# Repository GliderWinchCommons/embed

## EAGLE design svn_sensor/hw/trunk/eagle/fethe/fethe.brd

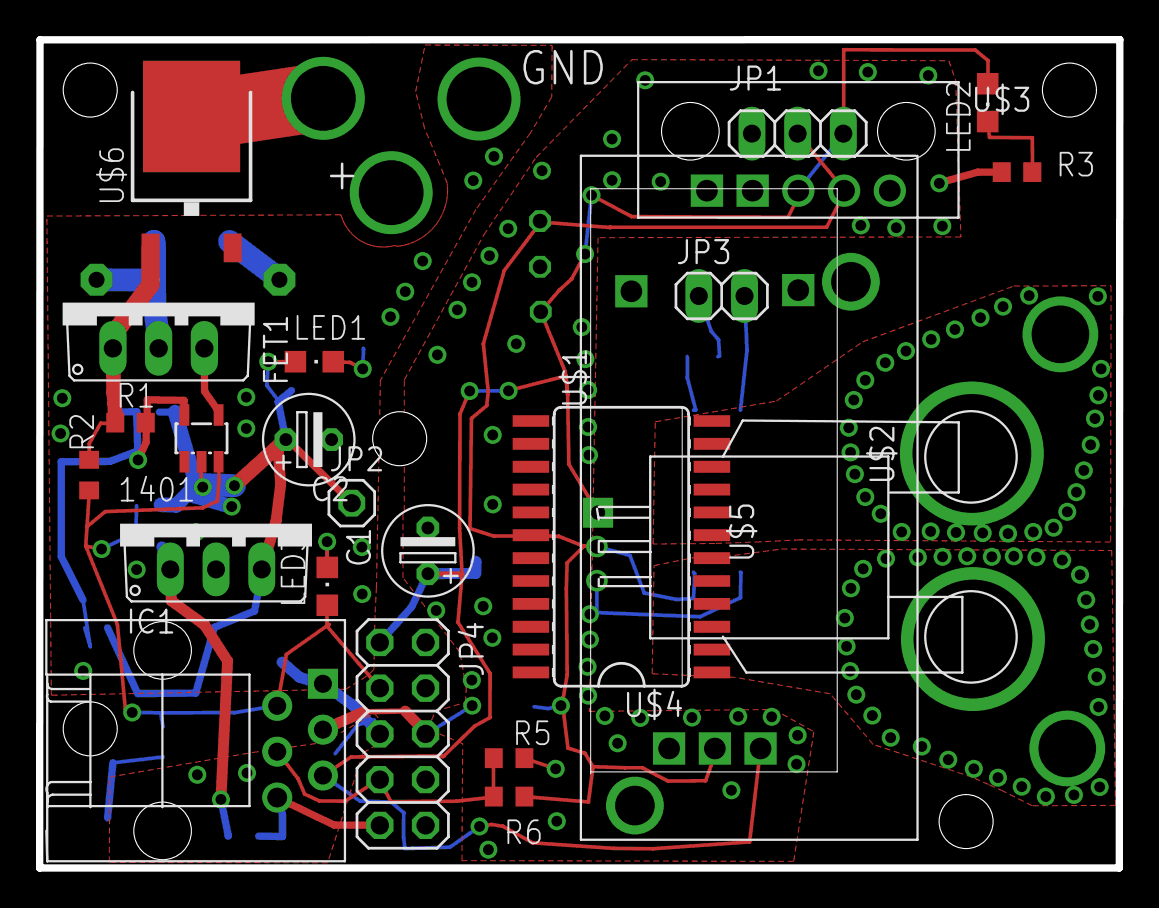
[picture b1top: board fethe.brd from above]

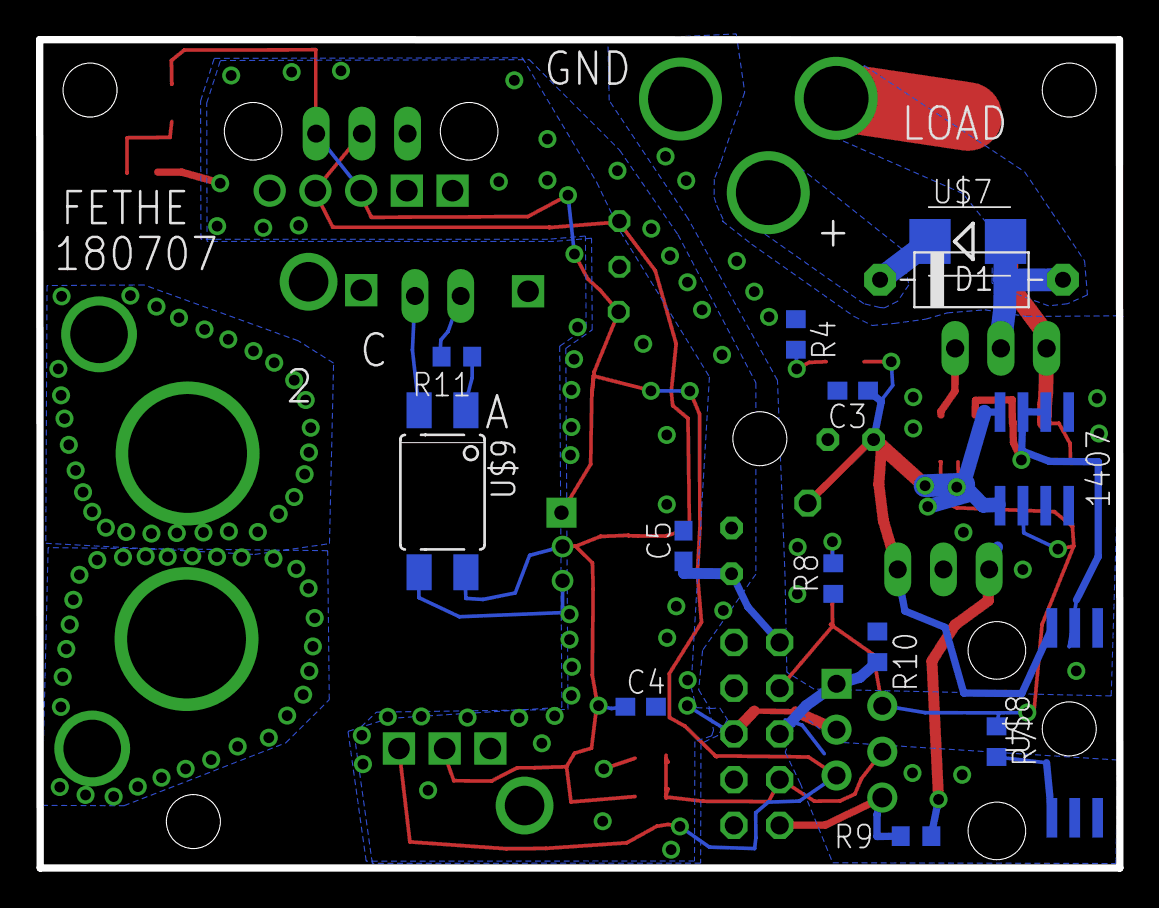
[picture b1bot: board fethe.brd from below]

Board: 2 copper layers, 60.0 x 46.0 mm, 38 parts (14 on the bottom side), 22 nets.

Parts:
1401: MCP1401; SOT23-5
1407: MCP1407; SO8
C1, C2: 10@25V; ES-2,5L
C3, C4, C5: 4.7u; C0603
D1: D-10
FET1: any1; TO220V
IC1: LM78xx; TO220V
JP1: 1X03
JP2: 1X01
JP3: 1X02
JP4: 2X05
LED1, LED2, LED3: CHIPLED_0805
R1: 4.7; R0603
R2, R9, R10: zero; R0603
R3, R6, R7, R8: 1K; R0603
R4, R11: 2.2K; R0603
R5: 3.3K; R0603
U$1: TAMURA_HE
U$2: ACS712MODULE
U$3: ACS711MODULE
U$4: ACS709/710; SO24W
U$5: ACS755
U$6: NFET-DT; D-PAK-4
U$7: B100LB; SMB_1
U$8: SI826; SDIP6
U$9: LTV817S; LTV316
U$25: MOD6P6C_1

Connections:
+5V: C1.1, C5.1, JP1.1, JP4.1, LED2.A, U$1.3, U$2.V, U$3.VCC, U$5.VCC, U$25.5
+10V: 1401.2, 1407.1, 1407.8, C2.1, C3.1, IC1.3, JP2.1, LED1.A, U$8.6
B5BUF: 1401.3, 1407.2, JP4.3, LED3.A, R2.2, R7.1, U$25.2
DIV1: JP4.7, R5.2, R6.1, U$25.4
DRV_OUT: 1401.5, 1407.6, 1407.7, R1.2, U$8.5
FET-DRAIN: D1.1, FET1.2, U$6.D, U$7.A
FET_DRIVE_1: FET1.1, R1.1, R2.1, U$6.G
GND: 1401.4, 1407.4, 1407.5, C1.2, C2.2, C3.2, C4.2, C5.2, FET1.3, IC1.2, JP1.3, JP4.6, R3.1, R4.1, R5.1, R8.1, R10.1, U$1.2, U$2.G, U$3.GND, U$3.GND1, U$4.15, U$4.22, U$5.VOUT, U$6.S, U$8.4, U$9.P$3, U$25.3
GNDFETDRV: JP4.5, R10.2, U$8.3, U$25.1
I+: U$4.1, U$4.2, U$4.3, U$4.4, U$4.5, U$4.6
I-: U$4.7, U$4.8, U$4.9, U$4.10, U$4.11, U$4.12
ISO_IN_A: R11.1, U$9.P$1
ISO_IN_C: JP3.2, U$9.P$2
ISO_IN_PLUS: JP3.1, R11.2
LED1: LED1.C, R4.2
LED2: LED2.C, R3.2
LED3: LED3.C, R8.2
POWER_PLUS: D1.2, U$7.C
SI826A: R7.2, U$8.1
VI_12V: JP4.9, R9.2, U$25.6
VOUT: C4.1, JP1.2, R6.2, U$1.1, U$2.O, U$3.OUT, U$4.18, U$5.GND, U$9.P$4
VRIN: IC1.1, R9.1

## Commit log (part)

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2017-03-12 work on changing Makefile(s) for latest launchpad compiler, and use ~/.arm_tools setup for setting PATH
2017-03-22 readme update
2017-03-26 added script
2017-03-26 script and docs
2017-03-26 check to be current
2017-03-26 add more doc stuff
2017-03-28 fixed ratechangecic for more than 10 digit tick values in svn_pod dateselect directory
2017-06-01 ublox prog work for POD 3, remove launchselect binary
2017-06-09 *v2c_ublox time debug save current status
2017-06-12 major revisions to Tim2 timing of pod_v2c_ublox version
2017-06-14 podv2c_ ublox Tim2_pod_se.c working. Logging time and pb time not correct
2017-06-16 pod_v2b_ublox and pod_v2c_ublox maybe OK, but more testing to be certain
2017-06-18 add pod_v2d appears to work
2017-06-23 corrections in ../embed/svn_pod/sw_PC/trunk/readbackformatter_deh and datesselect for extra digit in the timestamp
2017-07-18 Save work on shaft_encoder
2017-07-20 save/backup work in progress on shaft encoder
2017-07-26 save work--debugging shaft_encoder. Seems to work. long long to float issue is current
2017-07-27 lltoflt debugging
2017-08-01 Testing & debugging shaft_encoder. Studying jitter on encoder pulses at 3600 rpm.
2017-08-07 added missing file to git for shaft_encoder
2017-08-10 save work on shaft_encoder. Adding database parameters Not compile error-free
2017-08-14 shaft_encoder save work status--calibration parameter tables now compile and store to flash bug in vector 41 to be sorted out
2017-08-17 shaft_encoder, save work. status--calibrated CAN mgs working todo--fix hardware filters for command IDs
2017-08-26 save work w minor mods to tests embedded in shaft_encoder
2018-03-23 save work on ../sensor/se1 and engine sensor function unbundling
2018-03-23 db cleanup save work
2018-03-26 work on se1 database, Makefiles, and flashing tables in high memory
2018-03-28 save work on revisions of se1, and still a mess
2018-03-31 save work on se1. parameter tables printout is OK
2018-04-04 save work on se1 revisions
2018-04-05 save, backup work on se1
2018-04-07 save debug and test work on se1
2018-04-09 save work on se1. temperature, manifold, and throttle adc w calibration OK. High cic rate unexplained. CAN msging not working
2018-04-09 clean up monitoring output. Fixed cic rate problem. CAN needs debugging.
2018-04-12 save work on se1. polling msg working. rpm input capture problem. cangate w command added to display floats
2018-04-20 add missing files to se1
2018-04-21 missing files in co1_sensor_ublox reconstructed and appears-to-work. cangate command l modified for straight unix time
2018-04-23 start work on revision and update of se4_h with new directory shaft. This is the initial save of the intial work, not at compiles stage
2018-04-25 save/backup work on shaft.c
2018-04-27 save and backup work on sensor/shaft
2018-05-01 debug and test shaft.c continues. RPM scaling looking better.
2018-05-02 add iir filtering for heartbeat, but not tested. Backup work
2018-05-05 save work. Major revisions to histogram code in shaft.c compiles, but no testing nor debugging
2018-05-07 shaft.c histogram appearing to work. cangate command h works with it. Needs more testing and cleanup
2018-06-10 start Arduino f103 work
2018-06-12 save work on f103Ard eagle layout
2018-06-14 sensor/powerbox debugging started. Status USART1 working. Currently org at 0x08000000. ldrfixed requires some changes for limited ports and addresses out of range causing a hard fault
2018-06-18 struct PWRBOXLC and sql files with parameters updated. Needs debugging and high flash scripts to load parameters
2018-06-20 save debugging work
2018-06-21 CAN msgs working but low threshold alarm not tested
2018-06-23 modified make flash, openocd, in Makefiles to use 128K in powerbox
2018-06-26 save latest work
2018-06-29 f103Ard eagle layout complete, but needs review
2018-06-29 save revisions to f103Ard board layout. More review is prudent
2018-06-29 save eagle work
2018-07-01 f103Ard board additions. save work
2018-07-03 revised layout of f103Ard for better ADC noise
2018-07-04 f103Ard board, added 6P6C jacks
2018-07-06 fethe board layout started
2018-07-07 submod and fethe board layout save work
2018-07-09 save tweaks to f103Ard, fethe, submod board layouts
2018-07-10 small changes to board layouts, f103Ard, fethe
2018-07-11 add R11 for optocoupler
2018-07-12 minor changes to pcb layouts
2018-07-16 svn_sensor powerbox adc issue with dma and shifted data sorted out. CONT and DMA in CR2 setting delayed until end of calibration and DMA setup. Begin adding Hall-effect sensor w calibration
2018-07-17 save updates to powerbox. New calibrations for powerbox adcs. Hall-effect sensor CAN msg not yet implemented
2018-07-29 save current work
2018-08-02 save and update for minor changes
2018-09-06 cangate cmd q changed to show canid and CANID_INSERT.sql database name for incoming msgs
2018-09-19 save and backup minor tweaks
2018-10-04 update and fix parameter loading in co1_sensor_ublox
2018-10-06 fix db_updatej in svn_common trunk db to use GlinderWinchCommons and not GliderWinchItems
2018-10-11 svn_sensor PC cancnvt appears to work
2018-10-14 reverse ssh update work. README in svn_pod/sw_PC/trunk/tunnel-scripts has additional notes
2018-11-01 cleanup of downloading from POD after MT logging.
2018-11-14 save debugging work on dateselect and launchselect
2018-12-16 save before working on abort scheme for CAN driver
2019-03-28 repo missing can_hub in svn_common trunk added
2019-03-28 can_hub added
2019-04-04 Skype review. A few minor changes to can_driver.
2019-04-05 save original can_driver with abort debugging code jic
2019-05-05 canloglist added. First version without CAN ID names
2019-05-13 update test
2019-05-21 save work. cancnvtmatlab ready to begin debugging.
2019-05-25 cancnvtmatlab work. Added command line switches to skip listings, etc.
2019-05-30 add some comments on blue pill
2019-06-09 flyingcap eagle files added
2019-08-04 add cangateCON for testing contactor project located in GliderWinchItems conatctor repo
2019-08-06 save and back up days debugging
2019-08-07 save and back work on cangateCON
2019-09-04 cangateCON added description field for k command
2019-12-28 update CANID_INSERT, and other minor items.
2020-03-22 cancnvtmatlab updating
2020-03-25 cangateCON fixed wy6 dlc
2020-04-01 cancnvtmatlab updating txt files
2020-10-02 updates to CANID_INSERT.sql
2020-10-29 db update
2020-11-04 added columns to CANID for function instance and CANID within function. Assignments of instance and id within function needs review. Some obsolete CANIDs were commented out.
2020-11-09 save updates to db
2020-11-14 updates for levelwind in cangateCON
2020-11-16 cangateCON. revised cmd_h to display MC_STATE in ascii. Added half word to w command
2020-11-19 minor fixes to cangateCON
2021-06-27 hub-server compile warning fix
2022-02-01 add cangateBMS.
2022-02-03 Add sorting to cangateBMS d command
2022-05-03 minor changes to sql files
2022-05-04 ave and backup
2022-05-09 cangateBMS save work d command
2022-05-14 save work cangateBMS
2022-08-21 update changes for BMS CANid
2022-08-27 update CANID
2022-09-18 save and backup work
2022-09-22 save and backup
2022-09-25 save work on CAN loading
2022-12-27 cangateBMS fix
2023-01-06 changed cmd d
2023-01-12 remove binary
2023-01-24 cangateBMS work
2023-01-25 cangateBMS work on cmd e
2023-01-30 minor changes to cangateBMS
2023-07-25 updates to cangateBMS
2023-07-25 CANreadings updates
2023-08-14 Work on cangateBMS for polling. Revised commands a and e
2023-08-20 backup work
2023-08-24 cangateBMS e self-discharge and discharge test on-off working
2023-08-27 save work on cangate BMS
2023-08-28 cangateBMS revision to command a
2023-09-04 save cangateBMS work
2023-09-10 updated e and a commands for emc1 emc2
2023-09-23 added commands to cangateBMS
2023-09-25 save work on cangateBMS for E command
2023-10-07 save and backup. improvments on cangateBMS E command
2024-03-06 debugging cangateBMS C command
2024-04-05 remove .o files from repo in cangateBMS
2024-05-17 CANID_INSERT.sql work
2024-06-16 fix CANldr for Ubuntu 22.04
2024-06-26 updated pct CAN bus load for socket. Previous was for serial port.
2024-06-28 add missing files
2024-07-02 cmd t w ncurses added
2024-07-02 module summary moved to below cell reading lines. Seems-to-work. Adding temperature and charge/relaxation status might be useful
2024-07-03 added current and status bytes to cangateBMS
2024-07-04 add bit help file for command t
2024-07-04 minor cleanups to cangateBMS
2024-07-06 update jots
2024-07-07 update and push
2024-07-16 cangateBMS update
2024-07-21 added color highlight limits to cangateBMS
2024-08-04 add cmd v to cangateBMS
2024-08-06 update cangateBMS cmd v
2024-08-07 revise x and h commands
2024-08-07 fix cangateBMS ta command total pack voltage
2024-09-06 matches CANloader1/ldrfixedF446 at this same date.
2024-09-08 minor tweaks to CANldr1 sleep
2024-09-24 fixed ta ZX bit display
2024-09-27 save before switching os
2024-11-09 fixed cangateBMS q command
2024-11-13 update db
2024-11-13 add missing file
2024-11-17 fixed q, u, n commands in cangateBMS to reconize CAN ID of zero jic an error somewhere ends up sending one...which it did
2024-11-26 cancnvt update
2024-11-27 update comments
2024-12-12 update db for encoder CAN IDs
2024-12-12 db updatej update
2025-01-12 update CANldr1 to include CAN ID in payload when code is LDR_RESET. With this non-BMS nodes can be selectively reset when loading.
2025-02-15 update layout and select files for cancnvtmatlab
2025-02-26 db update from Ubuntu 16
2025-02-27 updated db
2025-03-09 update cancnvtmatlab before working on cangateBMS
2025-03-28 updates for adding BMS modules
2025-04-13 Work on E command for string charging. Update. More work needed, but somewhat working
2025-04-13 update work on cangateBMS E command. Charge cycle and completion seemed-to-work. More testing and tweaks needed.
2025-04-18 case statement compile for gsm in cancnvtmatlab
2025-04-19 cangateBMS E command seems-to-work
2025-04-25 cancnvtmatlab missing CAN msg in layout error msg revised
2025-05-16 minor changes to cangateBMS Ev command
2025-12-07 Added 0x32000000 CAN msg to cancnvtmatlab select and layout files
2025-12-09 Moved CL and sws columns in csvfieldselect251207.txt to be ahead of battery values in csvfieldselect251209.txt. 12/09/25 use csvlinelayout251207.txt csvfieldselect251209.txt
2026-01-21 CANldr1 for int fix for netbooks
2026-01-21 CANldr fix for int problem with netbooks
2026-02-05 In cangateBMS Add pg command and increase volts amps power to ELCON max.
2026-02-07 Change default volts and amps for p command in cangateBMS
2026-02-12 cangateBMS. Clean up some debugging printfs
2026-02-12 update cacangateBMS p command default to 260v
2026-02-16 Insert charge current override for test
2026-02-18 debugging cangateBMS E command for ELCON. Fix override current
2026-02-19 Update for debugging with gsm setup
2026-02-19 cangateBMS E command, add Er and modified Eo to allow entering volts and amps that override the values derived from the BMS module discovery
2026-02-20 cangateBMS update doing debugging of E commmand
2026-03-18 schematic sketch for upgraded gateway ftdi 2can that adds isolated CAN subboard
2026-03-30 cangateBMS, send cmd to all to turn off self-discharge mode if on when ELCON charging completes
2026-05-01 update check to see if changes to cangateBMS p command were pused
2026-05-05 update cangateBMS E command for debugging
2026-05-17 cangateBMS e command added sum of voltages option. E command still being modified
2026-05-19 turn off NOELCON in E command
2026-05-25 cangateBMS clean up E cmd first progress printout timing
2026-05-25 Turn off NOELCON
2026-05-26 cangateBMS E cmd upgrades from charge test run
2026-05-27 cangateBMS E cmd upgrades. after zoom session. 0.2 curent override
2026-05-28 minor cosmetic changes to cangateBMS
